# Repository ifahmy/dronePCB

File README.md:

# Tiny Drone Flight Controller PCB

This repository documents the design of a custom STM32-based nano drone flight controller, incorporating power management, 2.4 GHz radio, motion sensors, and brushed motor drivers. Designed for compatibility with **ArduPilot** and **Betaflight**.

---

## Microcontroller Unit (MCU)

- **STM32F722RET6**, selected for performance and documentation.
- 8 MHz HSE oscillator with tuning capacitors for STM32 and sensors.
- Power monitoring via voltage divider and ADC.
- On-board **SWDIO/SWCLK** for debugging and bootloader flashing (DFU mode via BOOT and RESET).
- **Decoupling capacitors** used throughout for stability under current spikes.

---

## MCU Pin Assignments

- Verified via STM32CubeIDE.
- PWM signals generated via hardware timers.
- Deconflicted JTAG and other peripheral capabilities.
- SPI used for IMU (vs I2C in Nano).
- Pin selections support both ArduPilot and Betaflight configurations.

---

## Sensors & Motor Drivers

- **IMU**: ICM-42688-P (connected via SPI3 for efficiency).
- **Barometer**: MS5611 (lower data rate, connected via I2C with pull-ups).
- **Motors**: Driven by SI2302 N-Channel MOSFETs (supports high-frequency PWM, no gate driver required).
- **Flyback protection**: SS14 Schottky diodes.
- **Gate protection**: 10Ω resistors to suppress transients.

---

## Power Regulation & Charging

- **Battery input** with reverse polarity protection.
- **MCP73831-2** for LiPo charging via USB (charge current ~40 mA with 24.9k resistor).
- **MCP1700** LDO regulator (2.8V output) for analog and digital circuits.
- **Ideal diode configuration** using PMOS + Schottky for automatic switching between USB and battery.

---

## 2.4 GHz Radio & USB Interface

- **nRF24L01+** radio connected to SPI1 with CE and CS via GPIO.
- External ¼-wave wire antenna (~1.25”) with matching network based on datasheet.
- **16 MHz oscillator** for the radio.
- **Micro-USB** interface with 27Ω series resistors.
- **PRTR5V0U2X** for USB ESD protection.

---

## PCB Design Overview

- 4-layer board:
  - Top and Bottom: Signal layers
  - Inner Layers: +2.8V and Ground
- Motor PWM routed in +2.8V layer due to limited space.

---

## Next Steps & Recommendations

- Order fabricated PCBs.
- Flash bootloader / firmware using DFU for Betaflight/ArduPilot.

### Future Improvements
- Migrate from 4-layer to 2-layer for cost/manufacturing optimization.
- Reroute motor gate PWM signals away from power planes if space allows.

---

## Bill of Materials (BOM)

For a full list, see the Bill of Materials Excel sheet. Sample entries:

| Ref | Description | Value | Manufacturer Part # | Digi-Key Part # |
|-----|-------------|--------|----------------------|-----------------|
| U1  | IMU         | ICM-42688-P | ICM-42688-P | 1428-ICM-42688-PTR-ND |
| U2  | Barometer   | MS5611-01BA | MS561101BA03-50 | 223-1622-1-ND |
| U3  | RF Radio    | nRF24L01+   | NRF24L01P-T | 4823-NRF24L01P-T-ND |

---

## Tools Used

- STM32CubeIDE (Pin config, firmware)
- KiCad 9.0  (PCB layout and schematic)
- DigiKey (Component sourcing)
- Calipers (Nano board dimensions)

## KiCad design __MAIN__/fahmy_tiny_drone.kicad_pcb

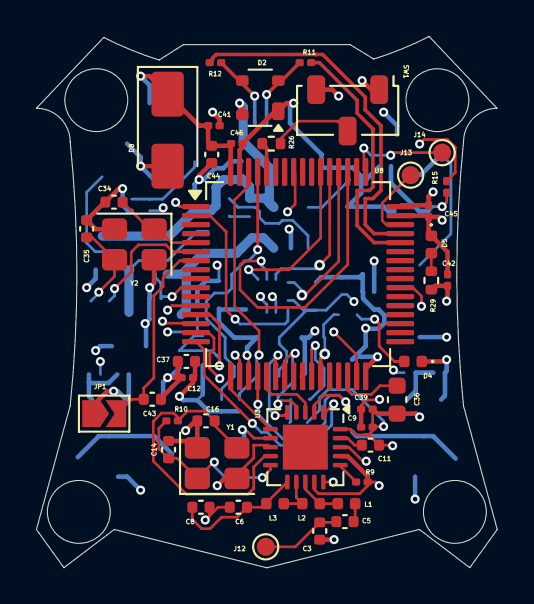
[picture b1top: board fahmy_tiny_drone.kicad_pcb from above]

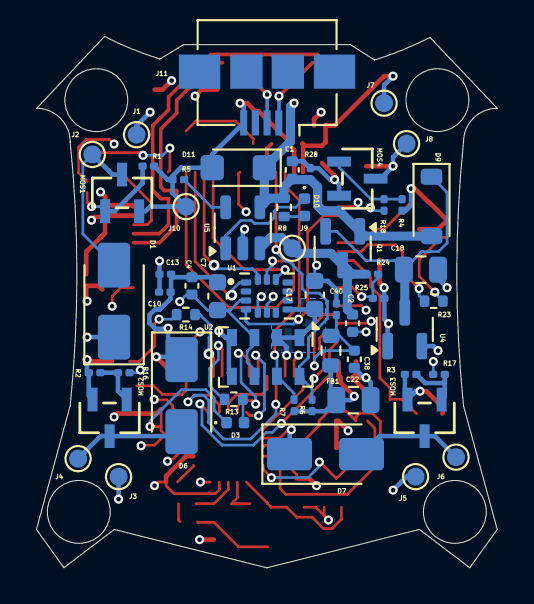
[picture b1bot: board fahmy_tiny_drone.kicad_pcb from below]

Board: 4 copper layers, 25.6 x 29.5 mm, 99 parts (56 on the bottom side), 62 nets.

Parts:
C1, C2, C37: 4.7u; C_0402_1005Metric
C3: 1p; C_0402_1005Metric
C4, C43: 0.1u; C_0402_1005Metric
C5: 1.5p; C_0402_1005Metric
C6: 2.2n; C_0402_1005Metric
C7, C17: 2.2u; C_0603_1608Metric
C8: 4.7p; C_0402_1005Metric
C9: 1n; C_0201_0603Metric
C10, C12: 10n; C_0201_0603Metric
C11: 33n; C_0402_1005Metric
C13, C39, C40, C41, C42, C45, C46: 100n; C_0201_0603Metric
C14, C16: 22p; C_0402_1005Metric
C18: 10u; C_0805_2012Metric
C22: 22u; C_0805_2012Metric
C34, C35: 10p; C_0402_1005Metric
C36: 4.7u; C_0603_1608Metric
C38, C44: 1u; C_0402_1005Metric
D1, D6, D7, D8: SS14; D_SMA
D2: PRTR5V0U2X; SOT-143
D3, D4, D5, D10: LED; LED_0402_1005Metric
D9: RB088LAM-40TFR; D_SOD-123
D11: SMF5V0A; D_SMF
FB1: 120R @ 100MHz; R_0603_1608Metric
J1: M1+; TestPoint_Pad_D1.0mm
J2: M1-; TestPoint_Pad_D1.0mm
J3: M2+; TestPoint_Pad_D1.0mm
J4: M2-; TestPoint_Pad_D1.0mm
J5: M3+; TestPoint_Pad_D1.0mm
J6: M3-; TestPoint_Pad_D1.0mm
J7: M4+; TestPoint_Pad_D1.0mm
J8: M4-; TestPoint_Pad_D1.0mm
J9: +BATT; TestPoint_Pad_D1.0mm
J10: GND; TestPoint_Pad_D1.0mm
J11: USB_B_Micro; USB_Micro-B_Amphenol_10104110_Horizontal
J12: ANT; TestPoint_Pad_D1.0mm
J13: SWDIO; TestPoint_Pad_D1.0mm
J14: SWCLK; TestPoint_Pad_D1.0mm
JP1: NRST; SolderJumper-2_P1.3mm_Open_TrianglePad1.0x1.5mm
L1: 3.9n; L_0402_1005Metric
L2: 8.2n; L_0402_1005Metric
L3: 2.7n; L_0402_1005Metric
MOS1, MOS2, MOS3, MOS4: SI2302-TP; SOT-23_MCC
Q1: DMG3415; SOT-23
R1, R2, R3, R4, R24: 10k; R_0201_0603Metric
R5: 24.9k; R_0201_0603Metric
R6, R7: 4.7k; R_0201_0603Metric
R8: 470; R_0402_1005Metric
R9: 22k; R_0201_0603Metric
R10: 1M; R_0201_0603Metric
R11, R12: 27; R_0201_0603Metric
R13, R14, R29: 330; R_0402_1005Metric
R15, R16, R17, R18: 10; R_0201_0603Metric
R23: 0R; R_0402_1005Metric
R25: 1k; R_0201_0603Metric
R26: 10k; R_0402_1005Metric
R28: 100K; R_0201_0603Metric
SW1: SW_SPDT; Nidec_Copal_CAS-120A
U1: ICM-42688-P; PQFN50P300X250X97-14N
U2: MS5611-01BA; LGA-8_3x5mm_P1.25mm
U3: nRF24L01P; QFN-20-1EP_4x4mm_P0.5mm_EP2.5x2.5mm
U4: MCP1700x-280xxTT; SOT-23
U5: MCP73831-2-OT; SOT-23-5
U8: STM32F722RET6; LQFP-64_10x10mm_P0.5mm
Y1: 16Mhz; Crystal_SMD_3225-4Pin_3.2x2.5mm
Y2: 8Mhz; Crystal_SMD_3225-4Pin_3.2x2.5mm

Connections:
+2.8V: C4.1, C7.1, C9.1, C10.1, C12.1, C13.1, C17.1, C22.1, C37.1, C39.1, C41.1, C42.1, C44.1, C45.1, C46.1, D1.1 (K), D6.1 (K), D7.1 (K), D8.1 (K), FB1.2, J1.1, J3.1, J5.1, J7.1, R6.1, R7.1, R29.1, SW1.3 (C), U1.5 (VDDIO), U1.8 (VDD), U2.1 (VDD), U2.2 (PS), U2.4 (CSB), U2.5 (CSB), U3.7 (VDD), U3.15 (VDD), U3.18 (VDD), U4.2 (VO), U8.1 (VBAT), U8.19 (VDD), U8.32 (VDD), U8.48 (VDD), U8.64 (VDD)
+BATT: C2.1, J9.1, Q1.3 (D), R24.1, U5.3 (V_{BAT})
/D+: D2.3 (I/O2), J11.2 (D-), R12.1
/D-: D2.2 (I/O1), J11.3 (D+), R11.1
/VCAP: C36.1, U8.30 (VCAP_1)
ADC_BATT: R24.2, R25.1, U8.10 (PC2)
BOOT0: R26.2, U8.60 (BOOT0)
Baro_I2C_SCL: R6.2, U2.8 (SCLK), U8.61 (PB8)
Baro_I2C_SDA: R7.2, U2.7 (SDI/SDA), U8.62 (PB9)
GND: C1.2, C2.2, C3.2, C4.2, C6.2, C7.2, C8.2, C9.2, C10.2, C11.1, C12.2, C13.2, C14.2, C16.2, C17.2, C18.2, C22.2, C34.2, C35.2, C36.2, C37.2, C38.2, C39.2, C40.2, C41.2, C42.2, C43.2, C44.2, C45.2, C46.2, D2.1 (GND), D3.1 (K), D4.1 (K), D5.1 (K), D11.2 (A2), J10.1, J11.5 (GND), JP1.1 (A), MOS1.2 (S), MOS2.2 (S), MOS3.2 (S), MOS4.2 (S), R1.2, R2.2, R3.2, R4.2, R5.2, R9.1, R25.2, R28.2, SW1.1 (A), U1.3 (RESV_3), U1.6 (GND), U2.3 (GND), U2.6 (SDO), U3.8 (VSS), U3.14 (VSS), U3.17 (VSS), U3.20 (VSS), U4.1 (GND), U5.2 (V_{SS}), U8.12 (VSSA), U8.18 (VSS), U8.31 (VSS), U8.47 (VSS), U8.63 (VSS), Y1.2, Y1.4, Y2.2, Y2.4
GYRO_CS: U1.12 (AP_CS), U8.54 (PD2)
GYRO_INT1: U1.4 (INT1/INT), U8.2 (PC13)
GYRO_MISO: U1.1 (AP_SDO/AP_AD0), U8.52 (PC11)
GYRO_MOSI: U1.14 (AP_SDA/AP_SDIO/AP_SDI), U8.53 (PC12)
GYRO_SCK: U1.13 (AP_SCL/AP_SCLK), U8.51 (PC10)
HSE_IN: C34.1, U8.5 (PH0), Y2.1
HSE_OUT: R23.1, U8.6 (PH1)
Motor 1: R15.1, U8.14 (PA0)
Motor 2: R16.1, U8.15 (PA1)
Motor 3: R17.1, U8.57 (PB5)
Motor 4: R18.1, U8.39 (PC8)
NRST: C43.1, JP1.2 (B), U8.7 (NRST)
unnamed: C5.1, L1.2
unnamed: C35.1, R23.2, Y2.3
unnamed: D1.2 (A), J2.1, MOS1.3 (D)
unnamed: D3.2 (A), R13.2
unnamed: D4.2 (A), R14.2
unnamed: D5.2 (A), R29.2
unnamed: D6.2 (A), J4.1, MOS2.3 (D)
unnamed: D7.2 (A), J6.1, MOS3.3 (D)
unnamed: D8.2 (A), J8.1, MOS4.3 (D)
unnamed: C18.1, D9.1 (K), Q1.2 (S), U4.3 (VI)
unnamed: D10.2 (A), R8.2
unnamed: D10.1 (K), U5.1 (STAT)
unnamed: C3.1, C5.2, J12.1
unnamed: MOS1.1 (G), R1.1, R15.2
unnamed: MOS2.1 (G), R2.1, R16.2
unnamed: MOS3.1 (G), R3.1, R17.2
unnamed: MOS4.1 (G), R4.1, R18.2
unnamed: R26.1, SW1.2 (B)
unnamed: L2.1, L3.2, U3.12 (ANT1)
unnamed: L1.1, L2.2, U3.13 (ANT2)
unnamed: C11.2, U3.19 (DVDD)
unnamed: R9.2, U3.16 (IREF)
unnamed: C6.1, C8.1, L3.1, U3.11 (VDD_PA)
unnamed: C14.1, R10.1, U3.10 (XC1), Y1.1
unnamed: C16.1, R10.2, U3.9 (XC2), Y1.3
unnamed: R5.1, U5.5 (PROG)
RADIO_CE: U3.1 (CE), U8.16 (PA2)
RADIO_CSN: U3.2 (CSN), U8.20 (PA4)
RADIO_INT: U3.6 (IRQ), U8.17 (PA3)
RADIO_MISO: U3.5 (MISO), U8.22 (PA6)
RADIO_MOSI: U3.4 (MOSI), U8.23 (PA7)
RADIO_SCK: U3.3 (SCK), U8.21 (PA5)
STATUS_LED1: R13.1, U8.26 (PB1)
STATUS_LED2: R14.1, U8.27 (PB2)
SWCLK: J14.1, U8.49 (PA14)
SWDIO: J13.1, U8.46 (PA13)
USB_D+: R12.2, U8.45 (PA12)
USB_D-: R11.2, U8.44 (PA11)
USB_VBUS: C1.1, D2.4 (VCC), D9.2 (A), D11.1 (A1), J11.1 (VBUS), Q1.1 (G), R8.1, R28.1, U5.4 (V_{DD})
VREF: C38.1, C40.1, FB1.1, U8.13 (VREF+)

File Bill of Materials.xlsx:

Item # | Reference | Qty | Description | Value | Footprint | Manufacturer PN | Digikey PN
1 | SW1 | 1 | SWITCH SLIDE SPDT 100MA 6V | SW_SPDT | Button_Switch_SMD:Nidec_Copal_CAS-120A | CAS-120A | CAS-120A-ND
2 | C9 | 1 | CAP CER 1000PF 25V X7R 0201 | 1n | Capacitor_SMD:C_0201_0603Metric | GRM033R71E102KA01D | 490-3184-1-ND
3 | C10,C12 | 2 | CAP CER 10000PF 25V X5R 0201 | 10n | Capacitor_SMD:C_0201_0603Metric | GRM033R61E103KA12D | 490-7194-1-ND
4 | C13,C39,C40,C41,C42,C45,C46 | 7 | CAP CER 0.1UF 6.3V X5R 0201 | 100n | Capacitor_SMD:C_0201_0603Metric | CL03A104KQ3NNNC | 1276-1013-1-ND
5 | C1,C2,C37 | 3 | CAP CER 4.7UF 6.3V X5R 0402 | 4.7u | Capacitor_SMD:C_0402_1005Metric | JMK105BBJ475MV-F | 587-2787-1-ND
6 | C3 | 1 | AP CER 1PF 50V C0G/NP0 0402 | 1p | Capacitor_SMD:C_0402_1005Metric | GJM1555C1H1R0BB01D | 490-6073-1-ND
7 | C4,C43 | 2 | CAP CER 0.1UF 10V X7R 0402 | 0.1u | Capacitor_SMD:C_0402_1005Metric | CL05B104KP5NNNC | 1276-1002-1-ND
8 | C5 | 1 | CAP CER 1.5PF 50V C0G/NP0 0402 | 1.5p | Capacitor_SMD:C_0402_1005Metric | 0402N1R5B500CT | 1292-1274-1-ND
9 | C6 | 1 | CAP CER 2200PF 50V X7R 0402 | 2.2n | Capacitor_SMD:C_0402_1005Metric | C0402C222J5RACTU | 399-C0402C222J5RACTUCT-ND
10 | C8 | 1 | CAP CER 4.7PF 50V C0G/NP0 0402 | 4.7p | Capacitor_SMD:C_0402_1005Metric | GRM1555C1H4R7CA01D | 490-5874-1-ND
11 | C11 | 1 | CAP CER 0.033UF 16V X7R 0402 | 33n | Capacitor_SMD:C_0402_1005Metric | GRM155R71C333KA01D | 490-3257-1-ND
12 | C14,C16 | 2 | CAP CER 22PF 50V C0G/NP0 0402 | 22p | Capacitor_SMD:C_0402_1005Metric | CL05C220JB51PNC | 1276-6849-1-ND
13 | C34,C35 | 2 | CAP CER 10PF 50V C0G/NPO 0402 | 10p | Capacitor_SMD:C_0402_1005Metric | CC0402JRNPO9BN100 | 311-1014-1-ND
14 | C38,C44 | 2 | CAP CER 1UF 6.3V X7R 0402 | 1u | Capacitor_SMD:C_0402_1005Metric | GRM155R70J105KA12D | 490-10024-1-ND
15 | C7,C17 | 2 | CAP CER 2.2UF 6.3V X7R 0603 | 2.2u | Capacitor_SMD:C_0603_1608Metric | CGA3E1X7R0J225K080AC | 445-6933-1-ND
16 | C36 | 1 | CAP CER 4.7UF 10V X5R 0603 | 4.7u | Capacitor_SMD:C_0603_1608Metric | CL10A475KP8NNNC | 1276-1044-1-ND
17 | C18 | 1 | CAP CER 10UF 10V X5R 0805 | 10u | Capacitor_SMD:C_0805_2012Metric | C0805C106K8PACTU | 399-C0805C106K8PACTUCT-ND
18 | C22 | 1 | CAP CER 22UF 6.3V X5R 0805 | 22u | Capacitor_SMD:C_0805_2012Metric | GRM21BR60J226ME39L | 490-1719-1-ND
19 | J11 | 1 | CONN RCPT USB2.0 MICRO B SMD R/A | USB_B_Micro | Connector_USB:USB_Micro-B_Amphenol_10104110_Horizontal | 10104110-0001LF | 609-4052-1-ND
20 | Y1 | 1 | CRYSTAL 16.000MHZ 22 PF SMD | 16Mhz | Crystal:Crystal_SMD_3225-4Pin_3.2x2.5mm | SXT32422AA48-16.000M | 2388-SXT32422AA48-16.000M-ND
21 | Y2 | 1 | CRYSTAL 8.0000MHZ 10PF SMD | 8Mhz | Crystal:Crystal_SMD_3225-4Pin_3.2x2.5mm | ECS-80-10-33-CGN-TR3 | 50-ECS-80-10-33-CGN-TR3CT-ND
22 | D1,D6,D7,D8 | 4 | DIODE SCHOTTKY 40V 1A DO214AC | SS14 | Diode_SMD:D_SMA | SS14 | 1655-SS14CT-ND
23 | D11 | 1 | TVS DIODE 5VWM 9.2VC DO219AB | SMF5V0A | Diode_SMD:D_SMF | SMF5V0A-M3-18 | 112-SMF5V0A-M3-18CT-ND
24 | D9 | 1 | DIODE SCHOTTKY 40V 5A PMDTM | RB088LAM-40TFR | Diode_SMD:D_SOD-123 | RB088LAM-40TFTR | 846-RB088LAM-40TFTRCT-ND
25 | U1 | 1 | MOTION SENSOR | ICM-42688-P | ICM_42688_P:PQFN50P300X250X97-14N | ICM-42688-P | 1428-ICM-42688-PTR-ND
26 | L1 | 1 | FIXED IND 3.9NH 750MA 0.14OHM SM | 3.9n | Inductor_SMD:L_0402_1005Metric | LQG15HS3N9B02D | 490-LQG15HS3N9B02DCT-ND
27 | L2 | 1 | FIXED IND 8.2NH 250MA 400MOHM SM | 8.2n | Inductor_SMD:L_0402_1005Metric | LRC0402CJ8N2GV001T | 712-LRC0402CJ8N2GV001TCT-ND
28 | L3 | 1 | FIXED IND 2.7NH 300MA 170MOHM SM | 2.7n | Inductor_SMD:L_0402_1005Metric | LRC0402CS2N7GV001T | 712-LRC0402CS2N7GV001TCT-ND
29 | D3,D4,D5,D10 | 4 | LED BLUE CLEAR 0402 SMD | LED | LED_SMD:LED_0402_1005Metric | 150040BS73240 | 732-11989-1-ND
30 | U3 | 1 | IC RF TXRX ISM>1GHZ 20QFN | nRF24L01P | Package_DFN_QFN:QFN-20-1EP_4x4mm_P0.5mm_EP2.5x2.5mm | NRF24L01P-T | 4823-NRF24L01P-T-ND
31 | U2 | 1 | SENSOR 17.4PSIA 24BIT | MS5611-01BA | Package_LGA:LGA-8_3x5mm_P1.25mm | MS561101BA03-50 | 223-1622-1-ND
32 | U8 | 1 | IC MCU 32BIT 512KB FLASH 64LQFP | STM32F722RET6 | Package_QFP:LQFP-64_10x10mm_P0.5mm | STM32F722RET6 | 497-17184-ND
33 | D2 | 1 | TVS DIODE 5.5VWM SOT143B | PRTR5V0U2X | Package_TO_SOT_SMD:SOT-143 | PRTR5V0U2X,215 | 1727-3884-1-ND
34 | Q1 | 1 | MOSFET P-CH 20V 4A SOT23-3 | DMG3415 | Package_TO_SOT_SMD:SOT-23 | DMG3415U-7 | DMG3415UDICT-ND
35 | U4 | 1 | IC REG LINEAR 2.8V 250MA SOT23-3 | MCP1700x-280xxTT | Package_TO_SOT_SMD:SOT-23 | MCP1700T-2802E/TT | MCP1700T-2802E/TTCT-ND
36 | U5 | 1 | IC BATT CNTL LI-ION 1CEL SOT23-5 | MCP73831-2-OT | Package_TO_SOT_SMD:SOT-23-5 | MCP73831T-2ACI/OT | MCP73831T-2ACI/OTCT-ND
37 | R1,R2,R3,R4,R24 | 5 | RES 10K OHM 1% 1/20W 0201 | 10k | Resistor_SMD:R_0201_0603Metric | RC0201FR-0710KL | 311-10.0KMCT-ND
38 | R5 | 1 | RES 24.9K OHM 1% 1/20W 0201 | 25k | Resistor_SMD:R_0201_0603Metric | RC0201FR-0724K9L | YAG2279CT-ND
39 | R6,R7 | 2 | RES 4.7K OHM 1% 1/20W 0201 | 4.7k | Resistor_SMD:R_0201_0603Metric | RMCF0201FT4K70 | RMCF0201FT4K70CT-ND
40 | R9 | 1 | RES 22K OHM 1% 1/20W 0201 | 22k | Resistor_SMD:R_0201_0603Metric | PFR03S-223-FNH | 2037-PFR03S-223-FNHCT-ND
41 | R10 | 1 | RES 1M OHM 5% 1/20W 0201 | 1M | Resistor_SMD:R_0201_0603Metric | WR02X105 JAL | 1292-WR02X105JALCT-ND
42 | R11,R12 | 2 | RES 27 OHM 5% 1/20W 0201 | 27 | Resistor_SMD:R_0201_0603Metric | RC0201JR-0727RL | YAG2291CT-ND
43 | R15,R16,R17,R18 | 4 | RES 10 OHM 1% 1/20W 0201 | 10 | Resistor_SMD:R_0201_0603Metric | RMCF0201FT10R0 | RMCF0201FT10R0CT-ND
44 | R25 | 1 | RES 1K OHM 1% 1/20W 0201 | 1k | Resistor_SMD:R_0201_0603Metric | RC0201FR-071KL | 311-1KMCT-ND
45 | R28 | 1 | RES SMD 100K OHM 0.5% 1/20W 0201 | 100K | Resistor_SMD:R_0201_0603Metric | ERJ-1RHD1003C | P15981CT-ND
46 | R8 | 1 | RES 470 OHM 1% 1/16W 0402 | 470 | Resistor_SMD:R_0402_1005Metric | RC0402FR-07470RL | 311-470LRCT-ND
47 | R13,R14,R29 | 3 | RES 330 OHM 1% 1/10W 0402 | 330 | Resistor_SMD:R_0402_1005Metric | RK73H1ETTP3300F | 2019-RK73H1ETTP3300FCT-ND
48 | R23 | 1 | RES SMD 0 OHM JUMPER 1/16W | 0R | Resistor_SMD:R_0402_1005Metric | RC1005J000CS | 1276-3480-1-ND
49 | R26 | 1 | RES 10K OHM 5% 1/16W 0402 | 10k | Resistor_SMD:R_0402_1005Metric | RC0402JR-0710KL | 311-10KJRCT-ND
50 | FB1 | 1 | FERRITE BEAD 120 OHM 0603 1LN | 120R @ 100MHz | Resistor_SMD:R_0603_1608Metric | MMZ1608S121ATA00 | 445-MMZ1608S121ATA00CT-ND
51 | MOSFET1,MOSFET2,MOSFET3,MOSFET4 | 4 | MOSFET N-CH 20V 3A SOT-23 | SI2302-TP | SOT-23_MCC | SI2302-TP | SI2302-TPMSCT-ND

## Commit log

2025-06-19 Initial upload of PCB Layout
2025-06-19 Added BOM
